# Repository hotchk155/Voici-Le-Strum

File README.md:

LE STRUM is a MIDI strummed chord control surface built around the PIC16F1825 microcontroller. 

The Le Strum documentation is at [http://six4pix.com/lestrum/](http://six4pix.com/lestrum/)

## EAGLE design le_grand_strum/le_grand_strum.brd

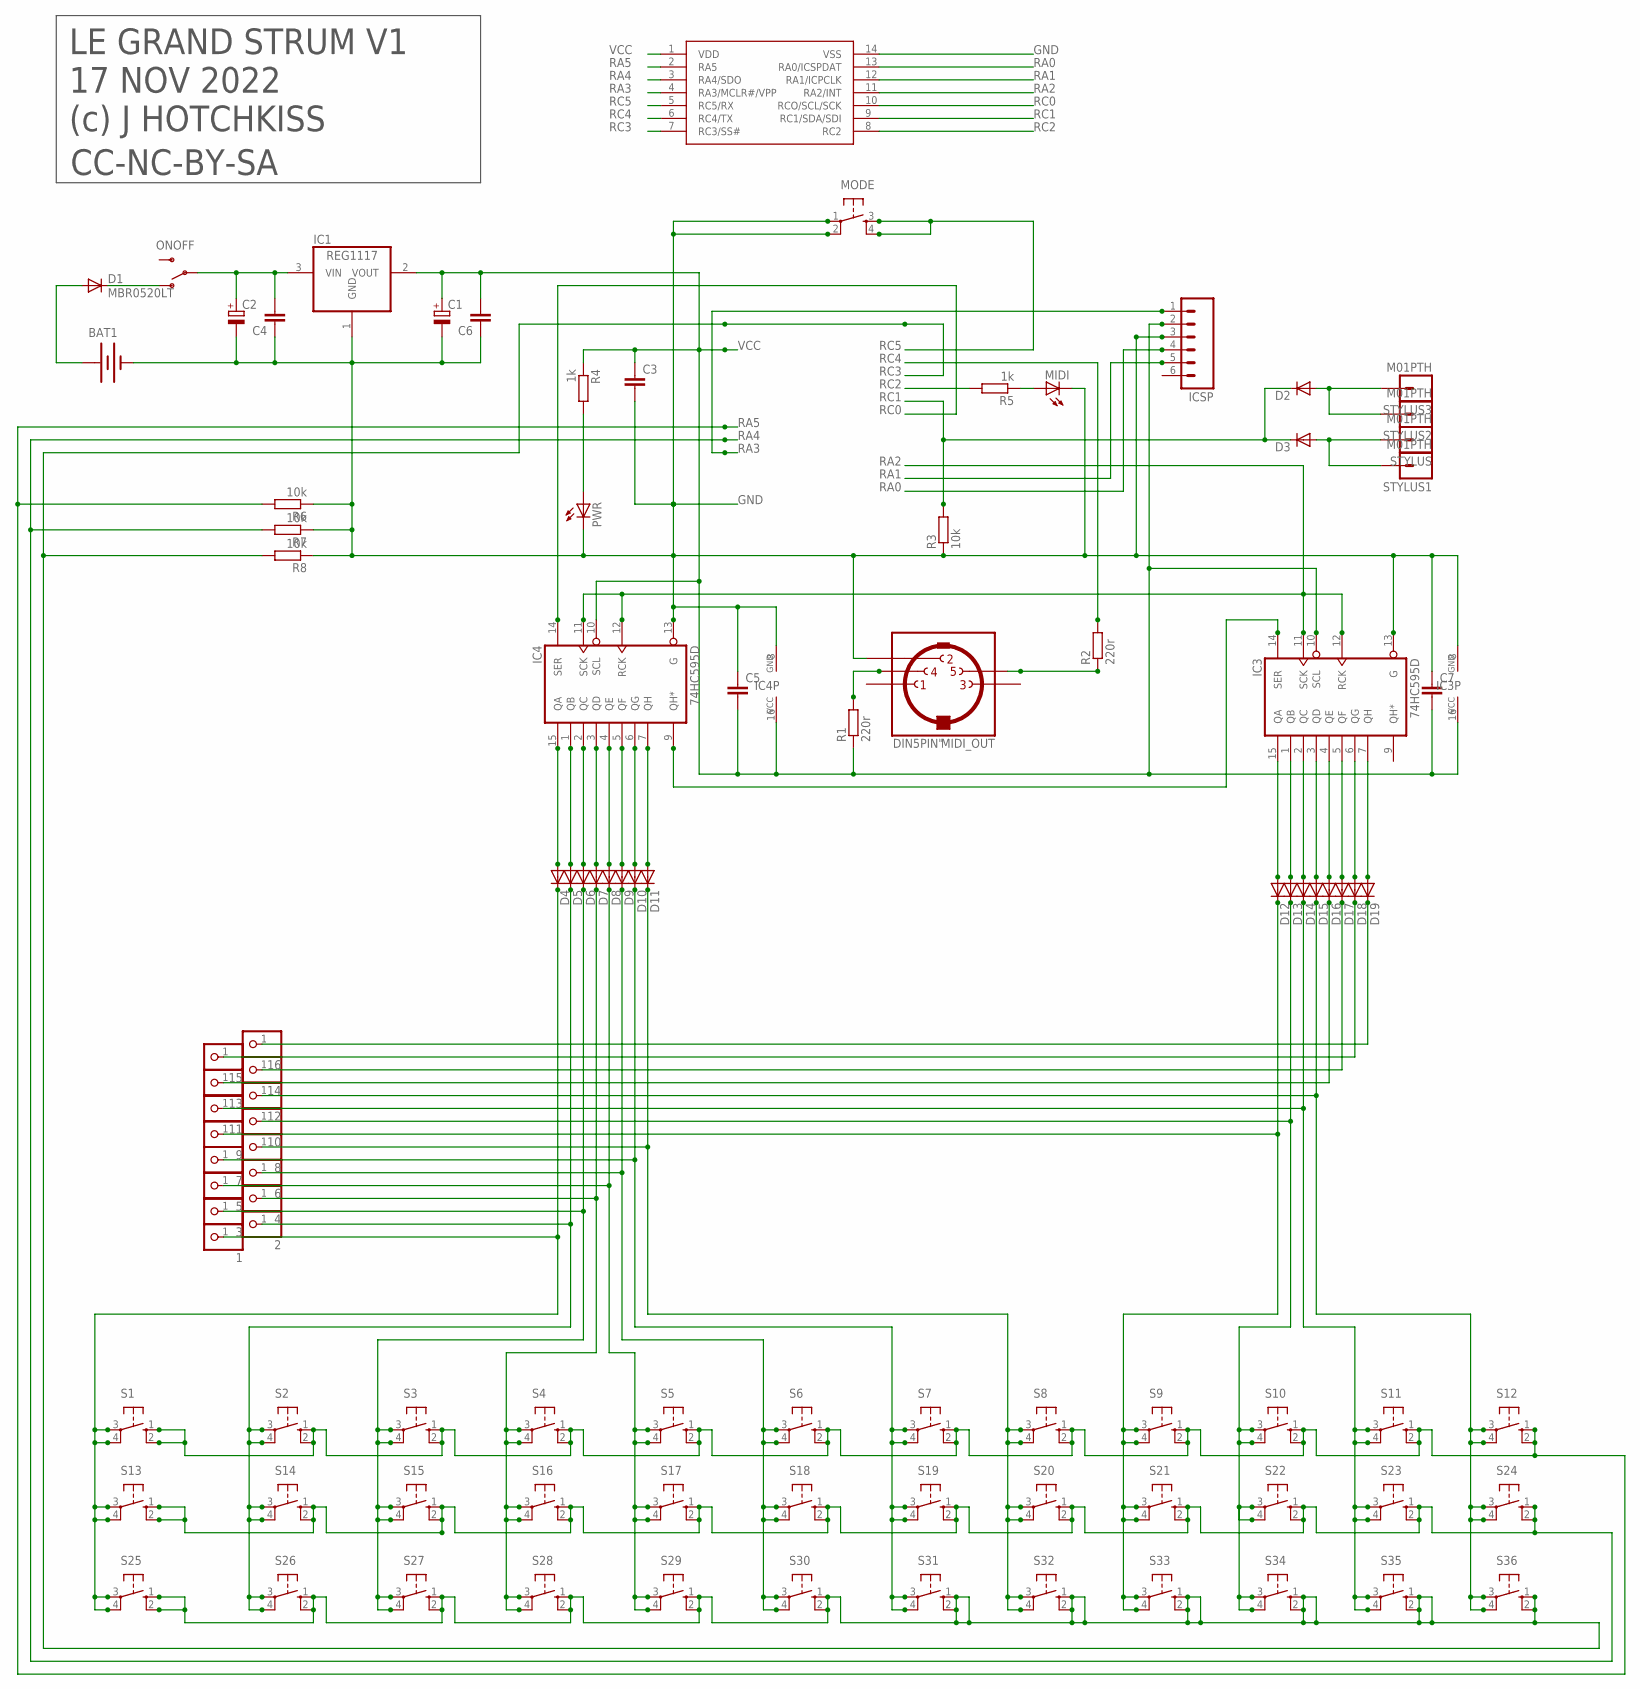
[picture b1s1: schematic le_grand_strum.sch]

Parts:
1, 2, 3, 4, 5, 6, 7, 8, 9, 10, 11, 12, 13, 14, 15, 16: PINHD-1X1; 1X01
BAT1: BATTERY2HOLES; PP3_BATTERBOX2
C1, C2: CPOL-EUE2-5; E2-5
C3, C4, C5, C6, C7: C-EUC0805; C0805
D1: MBR0520LT; SOD123
D2, D3, D4, D5, D6, D7, D8, D9, D10, D11, D12, D13, D14, D15, D16, D17, D18, D19: TS4148; D0805
IC1: REG1117; SOT223
IC2: PIC16F1825SO14; SO14
IC3, IC4: 74HC595D; SO16
ICSP: M06SIP; 1X06
MIDI: LEDCHIPLED_0805; CHIPLED_0805
MIDI_OUT: DIN5PIN"; TRUCONN90
MODE: TAC_SWITCHPTH; TACTILE-PTH
ONOFF: SWITCH-SPSTPTH; SWITCH-SPDT
PWR: LEDCHIPLED_0805; CHIPLED_0805
R1, R2: 220r; R0805
R3, R6, R7, R8: 10k; R0805
R4, R5: 1k; R0805
S1, S2, S3, S4, S5, S6, S7, S8, S9, S10, S11, S12, S13, S14, S15, S16, S17, S18, S19, S20, S21, S22, S23, S24, S25, S26, S27, S28, S29, S30, S31, S32, S33, S34, S35, S36: 40-XX; B3F-40XX
STYLUS, STYLUS1, STYLUS2, STYLUS3: M01PTH; 1X01

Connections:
CARRY: IC3.14 (SER), IC4.9 (QH*)
GND: BAT1.0V (-), C1.-, C2.-, C3.2, C4.1, C5.1, C6.1, C7.1, IC1.1 (GND), IC2.14 (VSS), IC3.8 (GND), IC3.13 (G), IC4.8 (GND), IC4.13 (G), ICSP.3, MIDI.C, MIDI_OUT.2, MODE.1, MODE.2, PWR.C, R3.1, R6.1, R7.1, R8.1
LINE1: 1.1, D4.K (C), S1.3, S1.4 (P1), S13.3, S13.4 (P1), S25.3, S25.4 (P1)
LINE2: 2.1, D5.K (C), S2.3, S2.4 (P1), S14.3, S14.4 (P1), S26.3, S26.4 (P1)
LINE3: 3.1, D6.K (C), S3.3, S3.4 (P1), S15.3, S15.4 (P1), S27.3, S27.4 (P1)
LINE4: 4.1, D7.K (C), S4.3, S4.4 (P1), S16.3, S16.4 (P1), S28.3, S28.4 (P1)
LINE5: 5.1, D8.K (C), S5.3, S5.4 (P1), S17.3, S17.4 (P1), S29.3, S29.4 (P1)
LINE6: 6.1, D9.K (C), S6.3, S6.4 (P1), S18.3, S18.4 (P1), S30.3, S30.4 (P1)
LINE7: 7.1, D10.K (C), S7.3, S7.4 (P1), S19.3, S19.4 (P1), S31.3, S31.4 (P1)
LINE8: 8.1, D11.K (C), S8.3, S8.4 (P1), S20.3, S20.4 (P1), S32.3, S32.4 (P1)
LINE9: 9.1, D12.K (C), S9.3, S9.4 (P1), S21.3, S21.4 (P1), S33.3, S33.4 (P1)
LINE10: 10.1, D13.K (C), S10.3, S10.4 (P1), S22.3, S22.4 (P1), S34.3, S34.4 (P1)
LINE11: 11.1, D14.K (C), S11.3, S11.4 (P1), S23.3, S23.4 (P1), S35.3, S35.4 (P1)
LINE12: 12.1, D15.K (C), S12.3, S12.4 (P1), S24.3, S24.4 (P1), S36.3, S36.4 (P1)
LINE13: 13.1, D16.K (C)
LINE14: 14.1, D17.K (C)
LINE15: 15.1, D18.K (C)
LINE16: 16.1, D19.K (C)
unnamed: PWR.A, R4.2
unnamed: BAT1.9V (+), D1.A
unnamed: D1.C, ONOFF.1 (O)
unnamed: D4.A, IC4.15 (QA)
unnamed: D5.A, IC4.1 (QB)
unnamed: D6.A, IC4.2 (QC)
unnamed: D7.A, IC4.3 (QD)
unnamed: D8.A, IC4.4 (QE)
unnamed: D9.A, IC4.5 (QF)
unnamed: D10.A, IC4.6 (QG)
unnamed: MIDI.A, R5.1
unnamed: D11.A, IC4.7 (QH)
unnamed: D12.A, IC3.15 (QA)
unnamed: D13.A, IC3.1 (QB)
unnamed: D14.A, IC3.2 (QC)
unnamed: D15.A, IC3.3 (QD)
unnamed: D16.A, IC3.4 (QE)
unnamed: D17.A, IC3.5 (QF)
unnamed: D18.A, IC3.6 (QG)
unnamed: D19.A, IC3.7 (QH)
unnamed: D2.A, STYLUS2.1, STYLUS3.1
unnamed: D3.A, STYLUS.1, STYLUS1.1
unnamed: MIDI_OUT.5, R2.1
unnamed: MIDI_OUT.4, R1.2
unnamed: C2.+, C4.2, IC1.3 (VIN), ONOFF.2
RA0: IC2.13 (RA0/ICSPDAT), ICSP.4
RA1: IC2.12 (RA1/ICPCLK), ICSP.5
RA2: IC2.11 (RA2/INT), IC3.11 (SCK), IC3.12 (RCK), IC4.11 (SCK), IC4.12 (RCK)
RA3: IC2.4 (RA3/MCLR#/VPP), ICSP.1
RA4: IC2.3 (RA4/SDO), R7.2, S13.1 (S), S13.2 (S1), S14.1 (S), S14.2 (S1), S15.1 (S), S15.2 (S1), S16.1 (S), S16.2 (S1), S17.1 (S), S17.2 (S1), S18.1 (S), S18.2 (S1), S19.1 (S), S19.2 (S1), S20.1 (S), S20.2 (S1), S21.1 (S), S21.2 (S1), S22.1 (S), S22.2 (S1), S23.1 (S), S23.2 (S1), S24.1 (S), S24.2 (S1)
RA5: IC2.2 (RA5), R6.2, S1.1 (S), S1.2 (S1), S2.1 (S), S2.2 (S1), S3.1 (S), S3.2 (S1), S4.1 (S), S4.2 (S1), S5.1 (S), S5.2 (S1), S6.1 (S), S6.2 (S1), S7.1 (S), S7.2 (S1), S8.1 (S), S8.2 (S1), S9.1 (S), S9.2 (S1), S10.1 (S), S10.2 (S1), S11.1 (S), S11.2 (S1), S12.1 (S), S12.2 (S1)
RC0: IC2.10 (RCO/SCL/SCK), IC4.14 (SER)
RC1: D2.K (C), D3.K (C), IC2.9 (RC1/SDA/SDI), R3.2
RC2: IC2.8 (RC2), R5.2
RC3: IC2.7 (RC3/SS#), R8.2, S25.1 (S), S25.2 (S1), S26.1 (S), S26.2 (S1), S27.1 (S), S27.2 (S1), S28.1 (S), S28.2 (S1), S29.1 (S), S29.2 (S1), S30.1 (S), S30.2 (S1), S31.1 (S), S31.2 (S1), S32.1 (S), S32.2 (S1), S33.1 (S), S33.2 (S1), S34.1 (S), S34.2 (S1), S35.1 (S), S35.2 (S1), S36.1 (S), S36.2 (S1)
RC4: IC2.6 (RC4/TX), R2.2
RC5: IC2.5 (RC5/RX), MODE.3, MODE.4
VCC: C1.+, C3.1, C5.2, C6.2, C7.2, IC1.2 (VOUT), IC2.1 (VDD), IC3.10 (SCL), IC3.16 (VCC), IC4.10 (SCL), IC4.16 (VCC), ICSP.2, R1.1, R4.1

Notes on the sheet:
LE GRAND STRUM V1
17 NOV 2022
(c) J HOTCHKISS
CC-NC-BY-SA

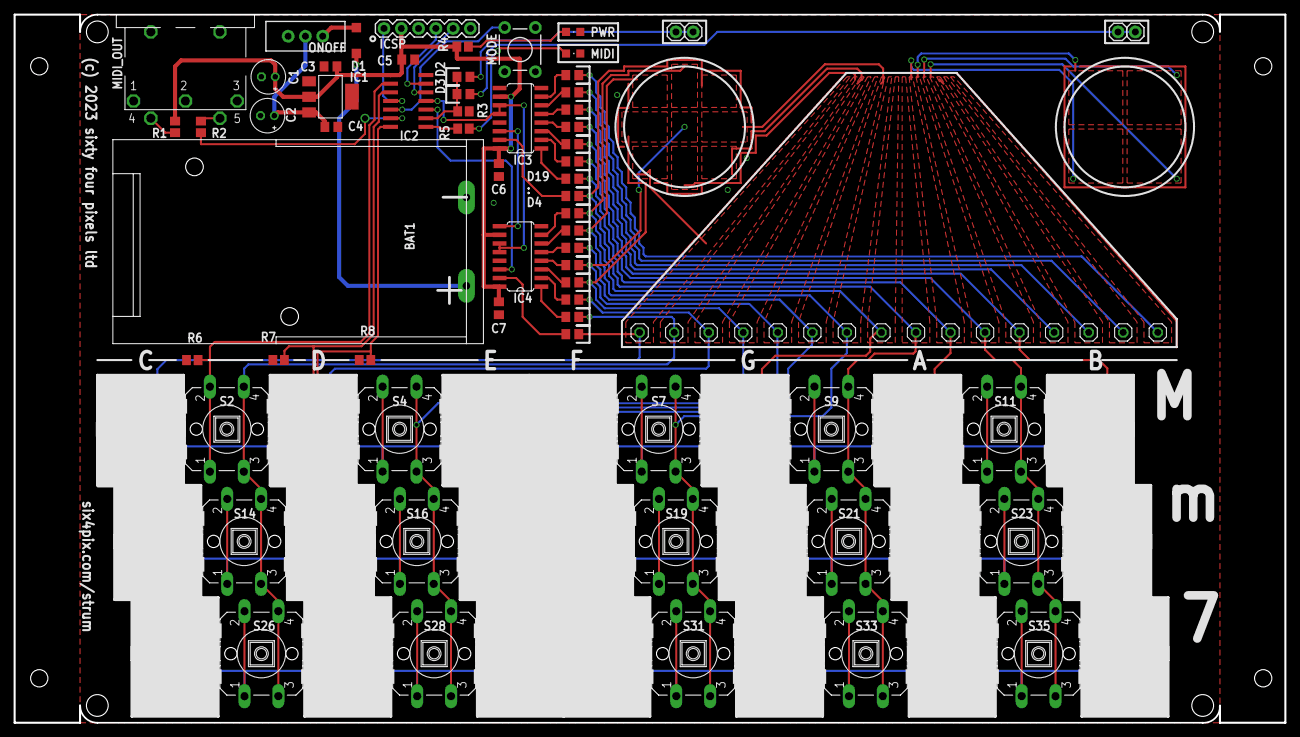
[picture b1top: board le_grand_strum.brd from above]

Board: 2 copper layers, 186.9 x 104.1 mm, 101 parts (0 on the bottom side), 56 nets.

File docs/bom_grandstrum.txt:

C3, C4, C5, C6, C7 		100nF 0805
D1      			MBR0520LT      
D2-D19				TS4148          
IC1      			REG1117
IC2      			PIC16F1825
IC3, IC4    			74HC595D
R1, R2       			220r
R3, R6, R7, R8       		10k
R4, R5       			1k

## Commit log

2013-02-12 actually - this should have been the first commit
2013-02-12 hardware
2013-02-12 changed to work with PIC16F1825 and new PCB
2013-02-12 working on chords/extensions
2013-02-12 more
2013-02-13 in work
2013-02-14 guitar mode stuff
2013-02-25 eagle updates
2013-05-22 gitignore
2013-05-22 stuff
2013-05-22 more stuff
2013-06-16 in progress
2013-06-16 Getting there!
2013-06-16 Version 1.00
2013-06-17 adding stuff
2013-06-19 build images
2013-06-22 fixes in firmware
2013-06-22 scale goodies
2013-06-22 load save user patch
2013-06-22 docs coming on
2013-06-22 presets
2013-06-23 docs
2013-06-23 1.1 hex
2013-06-28 schematic
2013-06-28 mod tips
2013-07-07 Version 1.2 - reverse strum
2013-07-07 tidy up
2013-07-07 Adding HEX file for build 1.2
2013-09-08 add CC license to file
2013-09-16 Version 1.3
    Add 1ms settling time
2013-12-07 docs change for v1.3
    just added 1.3 to quick ref card - no functional change
2014-01-11 userpics
2014-09-10 pics from martin sharrard
2014-10-09 pics
2014-10-16 Working on rev4
    Circle of 5ths mode
2014-10-27 rev 4
2014-10-27 Release 4
2015-01-29 pic from dustmason
2015-02-04 new quick ref
2015-04-12 stand
2016-01-06 case BOM added
2016-01-06 gitignore update
2016-04-11 Version 1.5
    Ability to change MIDI changes and transpose drone notes
2017-06-11 rename
2018-06-11 v5 packing slip
2018-08-21 Version 6
    Ability to set specific chord notes in "organ buttons" mode
2022-11-10 dfgfdfggfd
2022-11-11 dasasddads
2022-11-12 asads
2022-11-12 asddsa
2022-11-12 sdfsdf
2022-11-16 asasas
2022-11-17 REV 1
2022-11-17 FINAL V1
2022-11-17 even more final V1
2022-11-17 stencil
2023-01-11 rev2 board thru hole switches
2024-07-26 manual
2024-08-12 documentation updates
2024-11-19 VERSION 3
    ground midi out pin 2

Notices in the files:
le_grand_strum/le_grand_strum.brd:
(c) 2023 sixty four pixels ltd
